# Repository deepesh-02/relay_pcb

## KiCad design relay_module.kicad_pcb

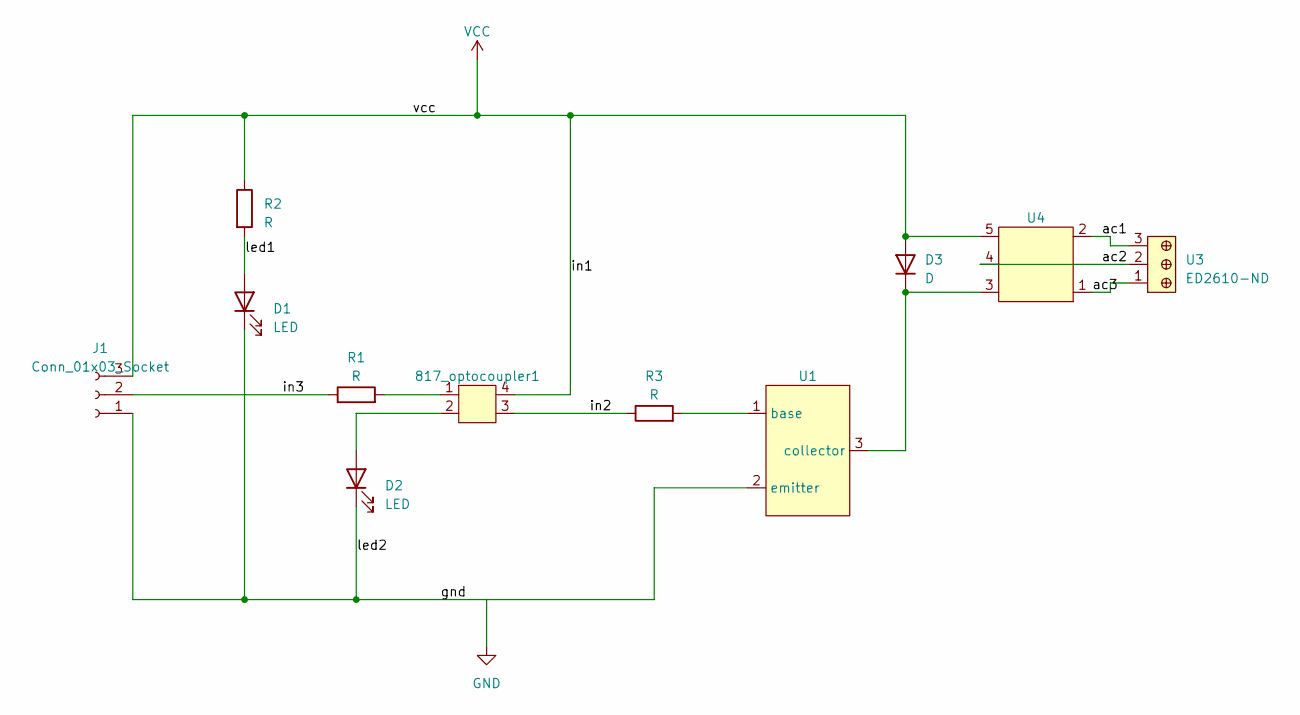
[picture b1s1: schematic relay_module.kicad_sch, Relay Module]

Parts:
817_optocoupler1: optocoupler
D1, D2: LED; LED_0805_2012Metric
D3: D; D_SMA
J1: Conn_01x03_Socket; PinHeader_1x03_P2.54mm_Vertical
R1, R2, R3: R; R_0805_2012Metric_Pad1.20x1.40mm_HandSolder
U1: smd_BC547
U3: ED2610-ND; TerminalBlock_bornier-3_P5.08mm
U4: relay

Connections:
/ac1: U3.3, U4.2
/ac2: U3.2, U4.4
/ac3: U3.1, U4.1
/gnd: D1.1 (K), D2.1 (K), J1.1, U1.2 (emitter)
/in2: 817_optocoupler1.3, R3.1
/in3: J1.2, R1.1
/led1: D1.2 (A), R2.2
unnamed: 817_optocoupler1.1, R1.2
unnamed: 817_optocoupler1.2, D2.2 (A)
unnamed: D3.1 (K), U1.3 (collector), U4.3
unnamed: R3.2, U1.1 (base)
VCC: 817_optocoupler1.4, D3.2 (A), J1.3, R2.1, U4.5

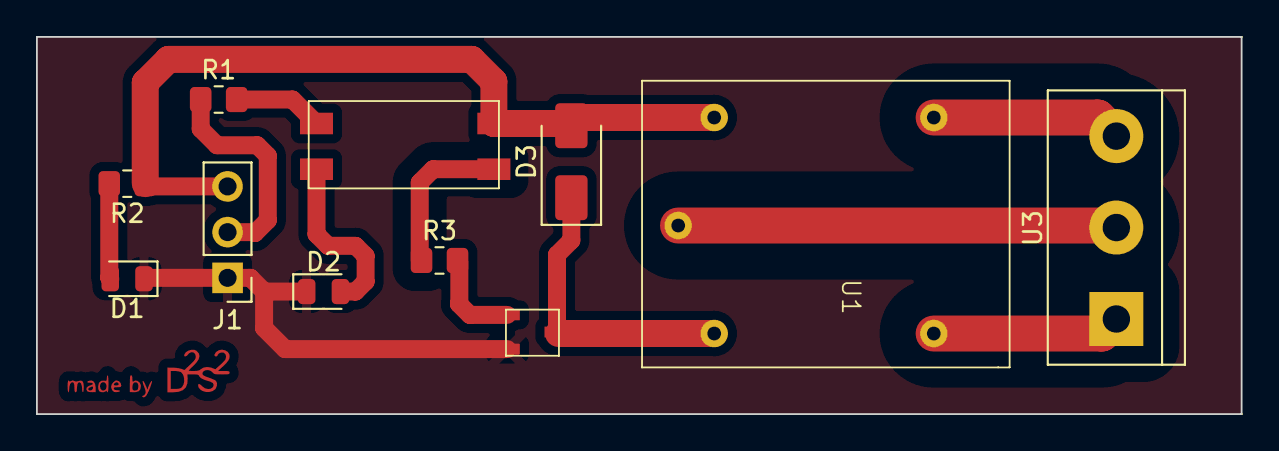
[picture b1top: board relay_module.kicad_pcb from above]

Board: 2 copper layers, 66.9 x 21.0 mm, 11 parts (0 on the bottom side), 12 nets.

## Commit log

2023-05-09 added files
2023-05-09 added two new files
